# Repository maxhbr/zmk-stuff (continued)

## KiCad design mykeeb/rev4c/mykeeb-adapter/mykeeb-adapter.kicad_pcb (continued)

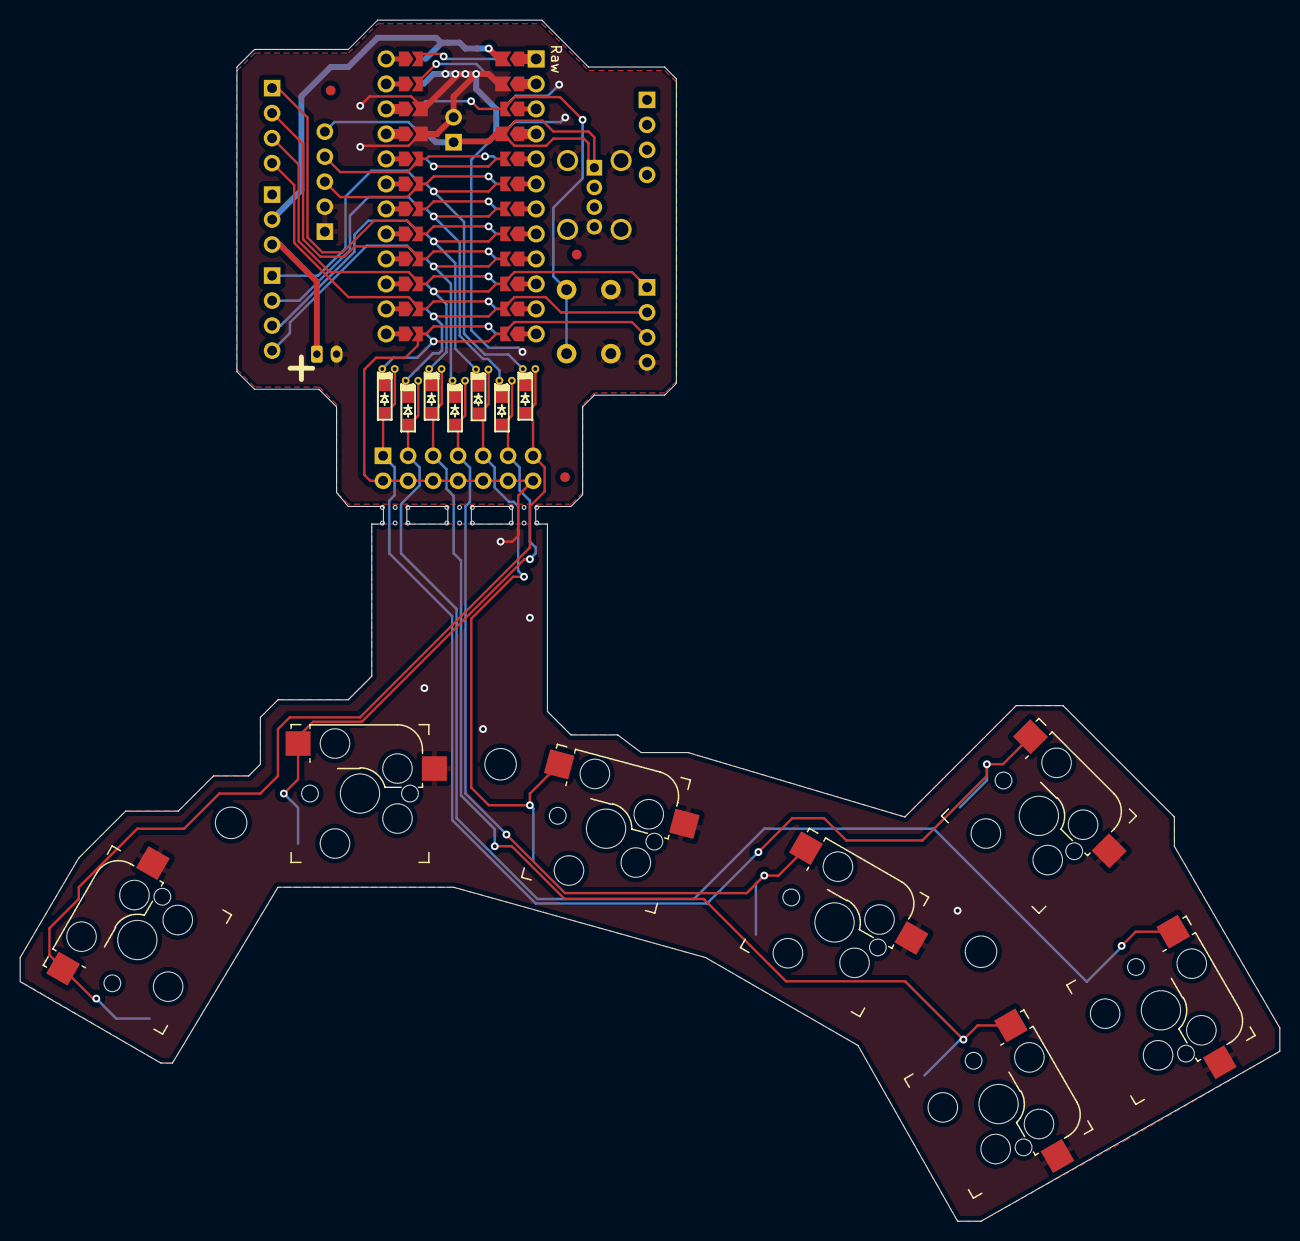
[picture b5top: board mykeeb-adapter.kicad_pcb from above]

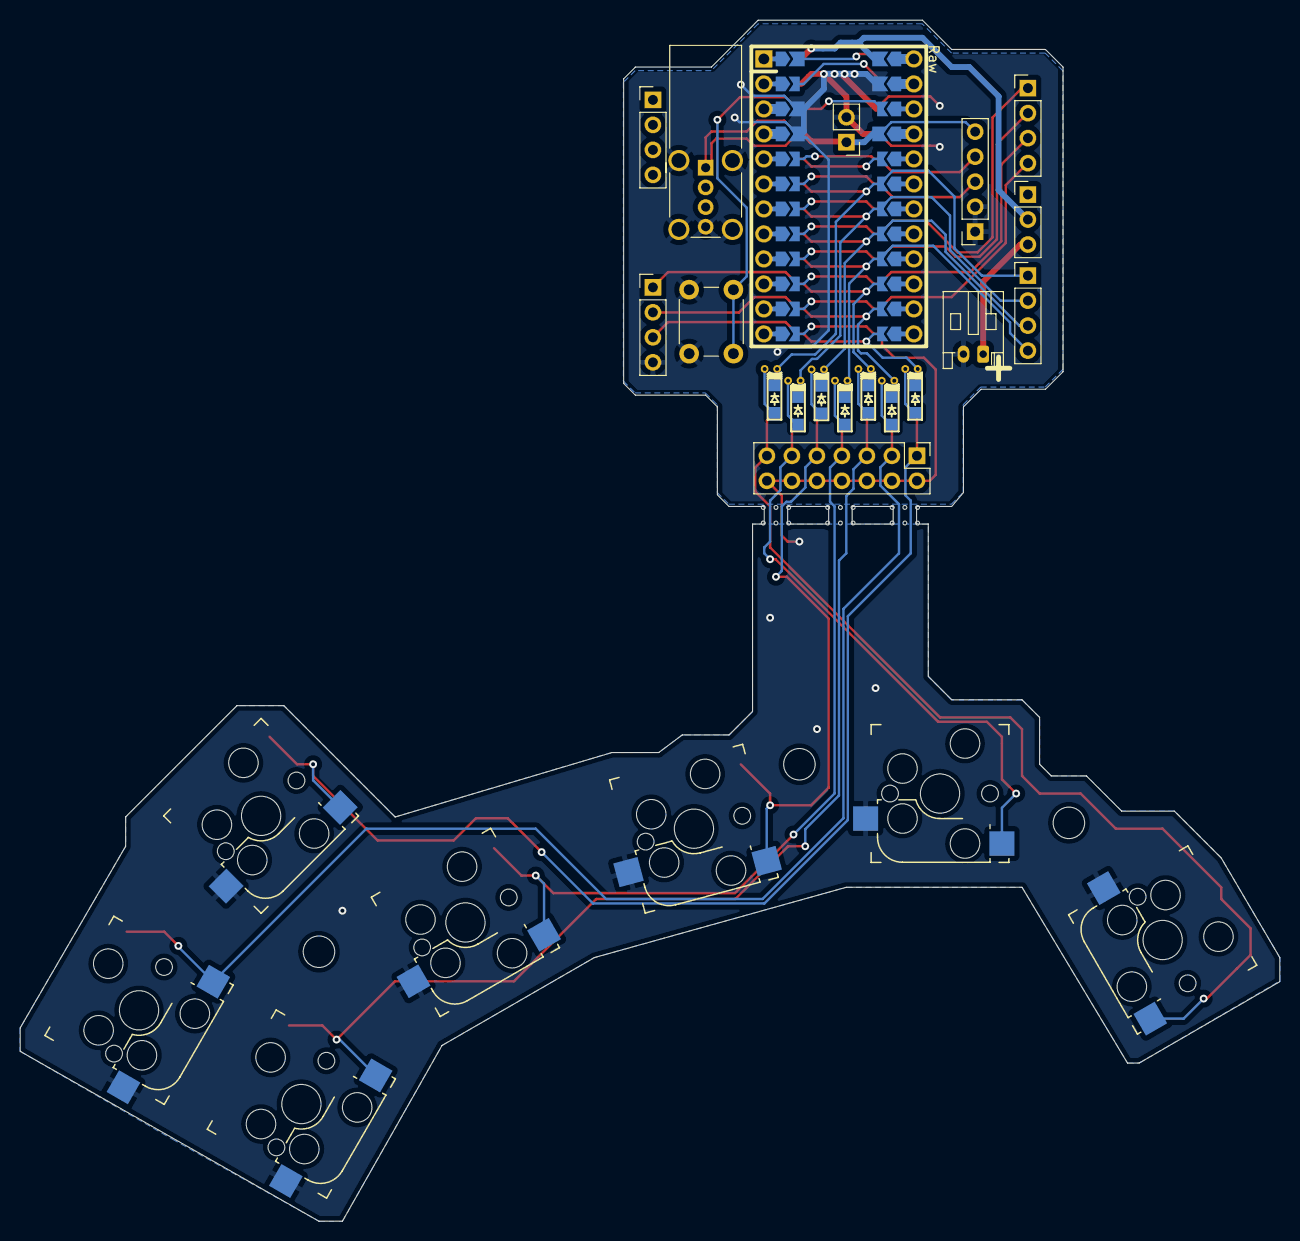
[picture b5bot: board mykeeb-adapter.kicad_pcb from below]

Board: 2 copper layers, 128.0 x 122.0 mm, 32 parts (8 on the bottom side), 26 nets.

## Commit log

2022-02-12 init
2022-02-12 add submodules
2022-02-15 add script to build zmk firmewares
2022-04-12 start merging all zmk configs in one repo
2022-04-12 add more configs to repo
2022-04-12 cleanup and move to single repo
2022-04-12 cleanup
2022-04-12 add some submodules
2022-04-13 clean up submodules
2022-04-13 add gitignore
2022-04-13 add mykeeb to this repo
2022-04-15 work on NYX
2022-04-16 wip on mykeeb
2022-04-18 add v0.1 pcb
2022-04-20 order rev1
2022-04-20 move rev1 to subfolder
2022-04-20 add case for mykeeb v1
2022-04-20 nonbreaking changes in rev1
2022-04-20 work on rev2
2022-04-24 wip on rev3
2022-04-28 rev3
2022-04-29 rev4b
2022-05-07 udpate
2022-05-08 commit rev4c gerbers
2022-05-09 shift is no enter :)
2022-07-11 add corne
2022-07-24 make wedge smaller
2022-08-06 update keymap
2022-08-15 update submodules
2022-08-24 commit rev5 (WIP)
2022-09-05 try to add sys layer
2023-04-02 add two new boards
2023-04-10 update taira keymap
2023-04-10 config to other repo
2023-05-08 add submodules and work on Readme
2023-05-08 add license
2023-05-08 init kicad project
2023-05-08 restructure
2023-05-16 routing
2023-05-17 top and bottom plate
2023-05-17 add gerber files for v7a2
2023-05-23 add choc v7a3
2023-05-24 finalize v7a3 for now
2023-05-24 add plates
2023-05-25 update gerbers, step 1
2023-05-25 update gerbers for v7a3
2023-05-29 start v7a4
2023-06-08 work on v7a5
2023-06-10 openscad? -> yes!
2023-06-10 add case
2023-06-11 work on case
2023-06-12 lipo switch
2023-06-13 add gerbers
2023-06-13 ordered v7a5
2023-06-13 render 3d models
2023-06-15 update stls
2023-06-16 support multiple tenting angles at once
2023-06-17 work on tent case??
2023-06-19 regenerate STLs
2023-06-21 fix the small 'MCU on the wrong side' issue
2023-06-22 yet another base?
2023-07-02 widen battery cutout
2023-07-02 rebuild stls
2023-07-16 update pcb after messup
